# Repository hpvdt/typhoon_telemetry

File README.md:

# Typhoon Telemetry

General template repository for our hardware projects, especially one-off and self-contained projects like custom test equipment. This template assumes that the hardware is being designed in KiCad.

## Organization

Pretty self-explanitory, put hardware related files into the `hardware` folder, firmware in the `firmware` folder. Other folders can be added as needed: for example a `media` folder is handy for storing pictures related to a project which can be used in documentation.

## Conventions

Partly for consistency, partly for functionality; please follow the following conventions:

- Try to keep folder names to single words and all lowercase
- Use underscores to separate words in names (e.g. `board_rev1`). **DO NOT USE SPACES! ESPECIALLY FOR FOLDERS CONTAINING CODE!** Spaces in file paths may cause issues in compilers and such so best to avoid them entirely.

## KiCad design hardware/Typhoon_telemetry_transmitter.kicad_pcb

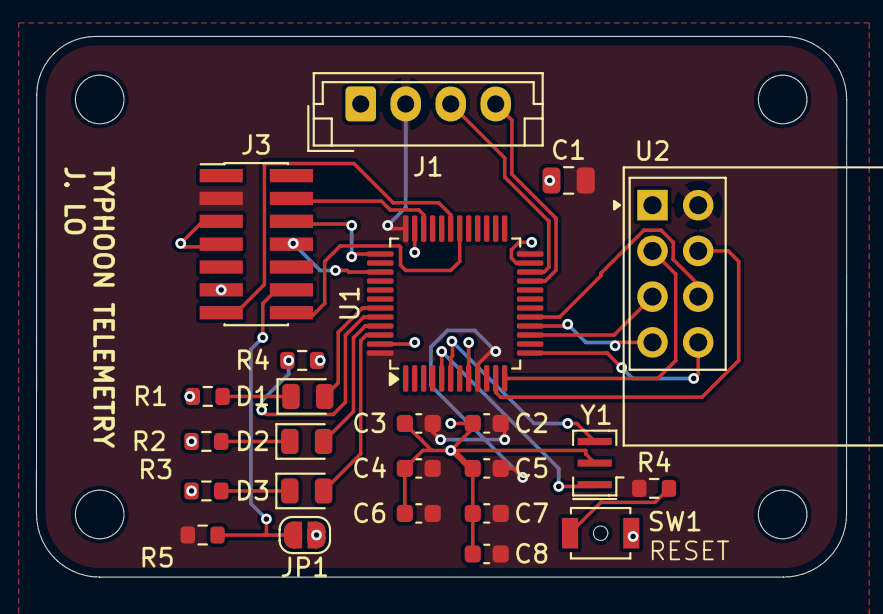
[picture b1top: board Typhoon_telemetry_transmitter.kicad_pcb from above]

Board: 2 copper layers, 45.0 x 30.0 mm, 28 parts (0 on the bottom side), 26 nets.

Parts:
C1: 10u; C_0805_2012Metric
C2, C3, C4, C5: 100n; C_0603_1608Metric
C6: 10n; C_0603_1608Metric
C7: 1u; C_0603_1608Metric
C8: 0.1u; C_0603_1608Metric
D1, D2, D3: LED; LED_0805_2012Metric
H1, H1#2, H1#3, H1#4: M2.5; MountingHole_2.7mm_M2.5
J1: Conn_01x04_Pin; JST_EH_B4B-EH-A_1x04_P2.50mm_Vertical
J3: Conn_ST_STDC14; PinHeader_2x07_P1.27mm_Vertical_SMD
JP1: Jumper_2_Open; SolderJumper-2_P1.3mm_Open_RoundedPad1.0x1.5mm
R1, R2, R3: 330; R_0603_1608Metric
R4, R4#2, R5: 10k; R_0603_1608Metric
SW1: SW_Push; SW_SPST_B3U-1000P-B
U1: STM32F103C8Tx; LQFP-48_7x7mm_P0.5mm
U2: NRF24L01_Breakout; nRF24L01_Breakout
Y1: 8M; Resonator_SMD_Murata_CSTxExxV-3Pin_3.0x1.1mm

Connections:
+3.3V: C1.2, C2.2, C3.2, C4.2, C5.2, C6.2, C7.2, C8.1, J1.2, J3.3 (VCC), R4.1, R5.1, U1.9 (VDDA), U1.24 (VDD), U1.36 (VDD), U1.48 (VDD), U2.2 (VCC)
/MISO: U1.16 (PA6), U2.7 (MISO)
/MOSI: U1.17 (PA7), U2.6 (MOSI)
/RF_EN: U1.12 (PA2), U2.3 (CE)
/RF_INT: U1.13 (PA3), U2.8 (IRQ)
/RF_SEL: U1.11 (PA1), U2.4 (~CSN)
/RX: J1.3, U1.22 (PB11)
/Reset: R4.2, SW1.2
/SCK: U1.15 (PA5), U2.5 (SCK)
/STLINK_{RX}: J3.13 (VCP_RX), U1.31 (PA10)
/STLINK_{TX}: J3.14 (VCP_TX), U1.30 (PA9)
/SWCLK: J3.6 (JCLK/SWCLK), U1.37 (PA14)
/SWDIO: J3.4 (JTMS/SWDIO), U1.34 (PA13)
/SWO: J3.8 (JTDO/SWO), U1.39 (PB3)
/TX: J1.4, U1.21 (PB10)
GND: C1.1, C2.1, C3.1, C4.1, C5.1, C6.1, C7.1, C8.2, J1.1, J3.5 (GND), J3.7 (GND), J3.11 (GNDDetect), JP1.1 (A), R1.1, R2.1, R3.1, R4#2.2, SW1.1, U1.8 (VSSA), U1.23 (VSS), U1.35 (VSS), U1.47 (VSS), U2.1 (GND), Y1.2
unnamed: D1.2 (A), U1.43 (PB7)
unnamed: D1.1 (K), R1.2
unnamed: D2.2 (A), U1.45 (PB8)
unnamed: D2.1 (K), R2.2
unnamed: D3.2 (A), U1.46 (PB9)
unnamed: D3.1 (K), R3.2
unnamed: J3.12 (~RST), JP1.2 (B), R5.2
unnamed: R4#2.1, U1.44 (BOOT0)
unnamed: U1.5 (PD0), Y1.1
unnamed: U1.6 (PD1), Y1.3

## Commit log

2024-09-07 Uploaded everything
2024-10-02 Updated debugger, pull down resistors
2024-10-05 Final Update
2024-10-05 Final Final Updates
2024-11-18 Final Update and Production done
